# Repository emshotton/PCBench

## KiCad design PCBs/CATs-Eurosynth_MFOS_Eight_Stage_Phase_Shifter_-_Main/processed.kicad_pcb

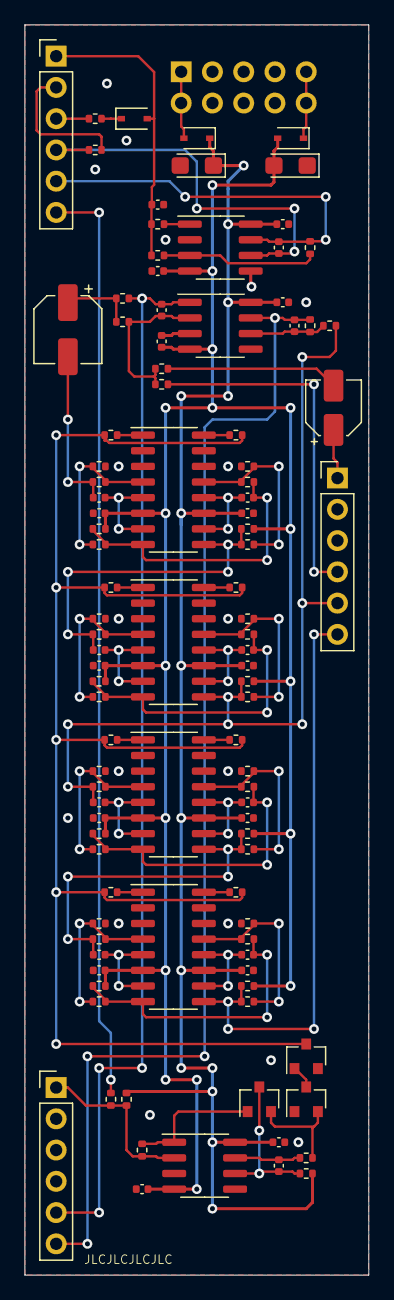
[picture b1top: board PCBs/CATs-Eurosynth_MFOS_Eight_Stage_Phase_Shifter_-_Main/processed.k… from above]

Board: 2 copper layers, 27.9 x 101.6 mm, 104 parts (1 on the bottom side), 62 nets.

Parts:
C1, C2, C3, C4, C5, C6, C8, C9, C10, C11, C12, C13, C14, C15: 100n; C_0402_1005Metric
C7, C16: 10µF/16V; CP_EIA-3216-18_Kemet-A
C17: 220n; C_0402_1005Metric
C18: 1µF/25V; CP_Elec_4x5.4
C19: 100p; C_0402_1005Metric
C20: 10µF/25V; CP_Elec_5x5.4
C21, C22, C23, C24, C25, C26, C27, C28: 4.7nF; C_0402_1005Metric
C29: 1µF/25V; C_0402_1005Metric
C30, C31: 22pF; C_0402_1005Metric
D1: 1N4148WS; D_SOD-323
D2, D3: 1N5817; D_SOD-323
J1: LFO; PinHeader_1x06_P2.54mm_Vertical
J2: CV_OUT; PinHeader_1x06_P2.54mm_Vertical
J3: In; PinHeader_1x06_P2.54mm_Vertical
J6: Power; Power_2x5_Vertical
Q1, Q3: MMBT3904; SOT-23
Q2: MMBT3906; SOT-23
R2, R5, R9, R14, R19, R33, R36, R39, R41, R55, R58, R60, R61: 10k; R_0402_1005Metric
R3: 43k; R_0402_1005Metric
R7: 270k; R_0402_1005Metric
R8, R31, R34, R37, R40, R51, R52, R53, R54: 1k; R_0402_1005Metric
R11: 430k; R_0402_1005Metric
R12, R17, R20: 100k; R_0402_1005Metric
R13: 1M; R_0402_1005Metric
R22: 2k; R_0402_1005Metric
R23, R25, R27, R29, R32, R35, R38, R42, R43, R45, R47, R49, R56, R57, R59, R62: 30k; R_0402_1005Metric
R24, R26, R28, R30, R44, R46, R48, R50, R64: 20k; R_0402_1005Metric
R65: 33k; R_0402_1005Metric
U1, U2, U3: TL072; SOIC-8_3.9x4.9mm_P1.27mm
U4, U5, U6, U7: LM13700; SOIC-16_3.9x9.9mm_P1.27mm

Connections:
+12V: C1.1, C2.1, C3.1, C4.1, C6.1, C7.1, C8.1, C12.1, D2.1, R11.2, R13.2, U1.8, U2.8, U3.8, U4.11, U5.11, U6.11, U7.11
+12V_In: D2.2, J6.+12V
-12V: C5.2, C9.2, C10.2, C11.2, C13.2, C14.2, C15.2, C16.2, D3.2, R33.1, R36.1, R39.1, R41.1, R55.1, R58.1, R60.1, R61.1, U1.4, U2.4, U3.4, U4.6, U5.6, U6.6, U7.6
-12V_In: D3.1, J6.-12V
CV: J2.1, R11.1, R12.1, R22.2, U3.2
Depth_CW: C17.1, J1.5, R20.1, U2.7
Depth_W: J1.6, R12.2
FB: J3.4, R9.2
GND: C1.2, C2.2, C3.2, C4.2, C5.1, C6.2, C7.2, C8.2, C9.1, C10.1, C11.1, C12.2, C13.1, C14.1, C15.1, C16.1, C29.2, J2.2, J2.3, J2.4, J3.2, J3.3, J6.GND, Q2.2, Q3.1, R31.1, R34.1, R37.1, R40.1, R51.1, R52.1, R53.1, R54.1, U1.3, U1.5, U2.2, U2.5, U3.3, U3.5, U4.3, U4.14, U5.3, U5.14, U6.3, U6.14, U7.3, U7.14
Iabc: Q2.3, R24.2, R26.2, R28.2, R30.2, R44.2, R46.2, R48.2, R50.2
In: C18.1, J3.1
Mode_In: J1.3, R8.1
Mode_Out: C17.2, J1.4, R17.1, U2.6
unnamed: C18.2, R5.2
unnamed: C19.1, R14.2, U3.7
unnamed: C19.2, Q1.3, R13.1, U3.6
unnamed: C20.1, R19.1, R65.2
unnamed: C21.1, U4.5, U4.7
unnamed: C22.1, U4.10, U4.12
unnamed: C22.2, R25.2, R32.1, R33.2, U4.8
unnamed: C23.1, U5.5, U5.7
unnamed: C23.2, R27.2, R35.1, R36.2, U4.9
unnamed: C24.1, U5.10, U5.12
unnamed: C24.2, R29.2, R38.1, R39.2, U5.8
unnamed: C25.1, U6.5, U6.7
unnamed: C26.1, U6.10, U6.12
unnamed: C26.2, R45.2, R55.2, R56.1, U6.8
unnamed: C27.1, U7.5, U7.7
unnamed: C27.2, R47.2, R57.1, R58.2, U6.9
unnamed: C28.1, U7.10, U7.12
unnamed: C28.2, R49.2, R59.1, R60.2, U7.8
unnamed: C30.2, R5.1, R9.1, R19.2, U1.2
unnamed: C31.2, R2.1, R3.2, U1.6
unnamed: D1.1, R8.2
unnamed: Q1.1, R22.1, U3.1
unnamed: Q1.2, Q3.2, R14.1
unnamed: Q2.1, Q3.3
unnamed: R7.2, R20.2, U2.3
unnamed: R23.1, R31.2, R32.2, U4.4
unnamed: R24.1, U4.1
unnamed: R25.1, R34.2, R35.2, U4.13
unnamed: R26.1, U4.16
unnamed: R27.1, R37.2, R38.2, U5.4
unnamed: R28.1, U5.1
unnamed: R29.1, R40.2, R42.2, U5.13
unnamed: R30.1, U5.16
unnamed: R43.1, R51.2, R56.2, U6.4
unnamed: R44.1, U6.1
unnamed: R45.1, R52.2, R57.2, U6.13
unnamed: R46.1, U6.16
unnamed: R47.1, R53.2, R59.2, U7.4
unnamed: R48.1, U7.1
unnamed: R49.1, R54.2, R62.2, U7.13
unnamed: R50.1, U7.16
unnamed: R64.2, U2.1
OUT4: C25.2, J3.5, R2.2, R41.2, R42.1, R43.2, U5.9
OUT8: J3.6, R61.2, R62.1, U7.9
Out1: C30.1, J2.5, R65.1, U1.1
Out2: C31.1, J2.6, R3.1, U1.7
PSS_In: C20.2, C21.2, R23.2
Rate_CW: C29.1, D1.2, J1.1, R7.1, R64.1
Rate_W: J1.2, R17.2

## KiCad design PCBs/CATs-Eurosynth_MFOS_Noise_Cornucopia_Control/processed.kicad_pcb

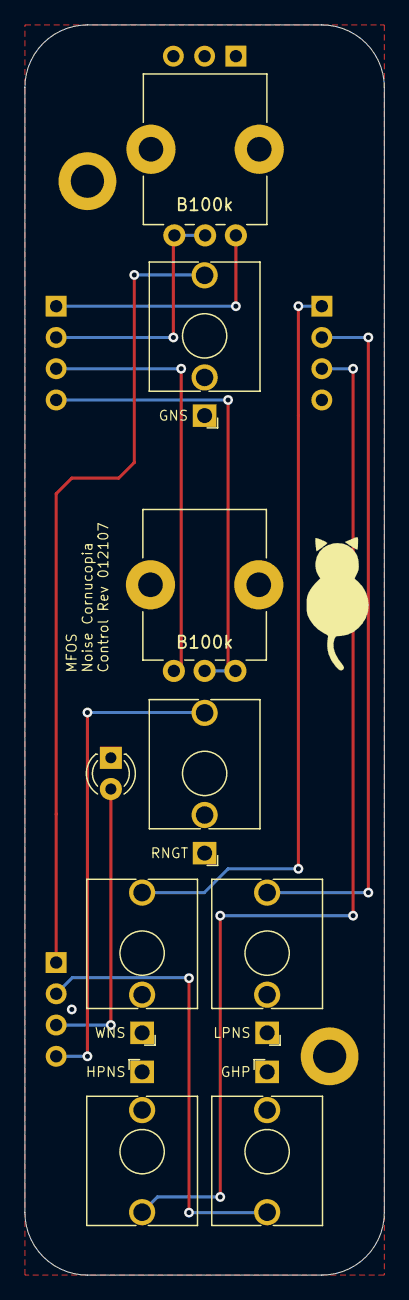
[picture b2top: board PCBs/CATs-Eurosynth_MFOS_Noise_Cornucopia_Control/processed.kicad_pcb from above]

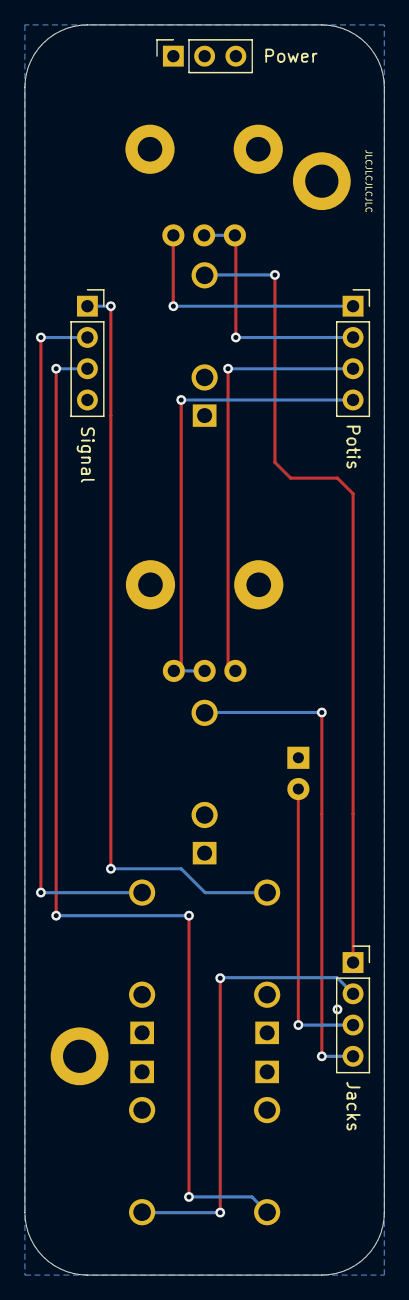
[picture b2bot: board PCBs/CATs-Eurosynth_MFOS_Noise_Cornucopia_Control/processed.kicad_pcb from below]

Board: 2 copper layers, 29.2 x 101.6 mm, 15 parts (4 on the bottom side), 12 nets.

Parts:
D1: LED; LED_D3.0mm
H1, H2: MountingHole_Pad; MountingHole_2.7mm_M2.5_DIN965_Pad
J1: WNS; Jack_3.5mm_QingPu_WQP-PJ398SM_Vertical_CircularHoles
J2: Power; PinSocket_1x03_P2.54mm_Vertical
J3: Signal; PinSocket_1x04_P2.54mm_Vertical
J4: LPNS; Jack_3.5mm_QingPu_WQP-PJ398SM_Vertical_CircularHoles
J5: HPNS; Jack_3.5mm_QingPu_WQP-PJ398SM_Vertical_CircularHoles
J6: Potis; PinSocket_1x04_P2.54mm_Vertical
J7: Jacks; PinSocket_1x04_P2.54mm_Vertical
J8: GNS; Jack_3.5mm_QingPu_WQP-PJ398SM_Vertical_CircularHoles
J9: GHP; Jack_3.5mm_QingPu_WQP-PJ398SM_Vertical_CircularHoles
J10: RNGT; Jack_3.5mm_QingPu_WQP-PJ398SM_Vertical_CircularHoles
R18, R28: B100k; Potentiometer_Alps_RK09K_Single_Vertical

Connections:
GHP: J7.2, J9.T
GND: D1.1, H1.1, H2.1, J1.S, J2.2, J4.S, J5.S, J8.S, J9.S, J10.S
GNS: J7.1, J8.T
GRNS1: J6.1, R18.1
GRNS2: J6.2, R18.2, R18.3
GTF1: J6.3, R28.3
GTF2: J6.4, R28.1, R28.2
HPNS: J3.3, J5.T
LEDA: D1.2, J7.3
LPNS: J3.2, J4.T
RNGT: J7.4, J10.T
WNS: J1.T, J3.1

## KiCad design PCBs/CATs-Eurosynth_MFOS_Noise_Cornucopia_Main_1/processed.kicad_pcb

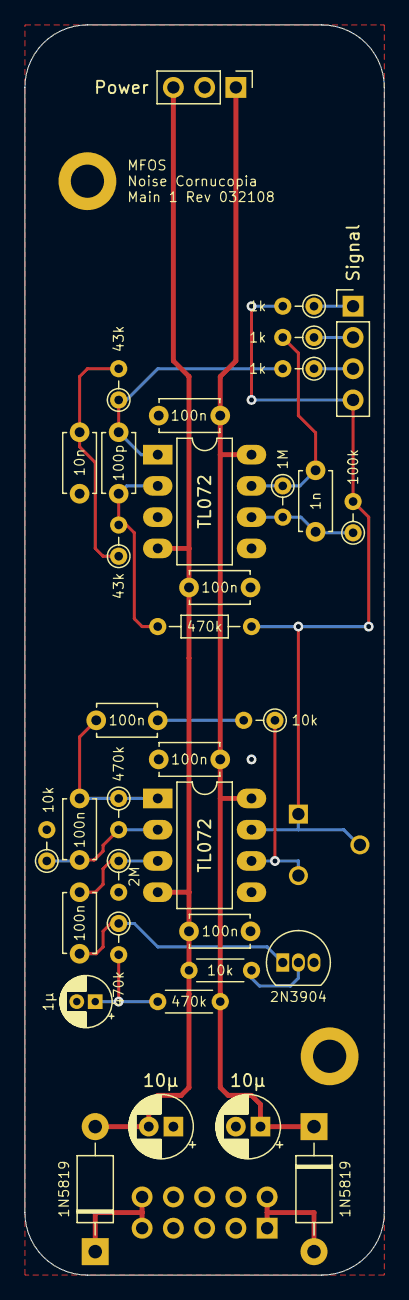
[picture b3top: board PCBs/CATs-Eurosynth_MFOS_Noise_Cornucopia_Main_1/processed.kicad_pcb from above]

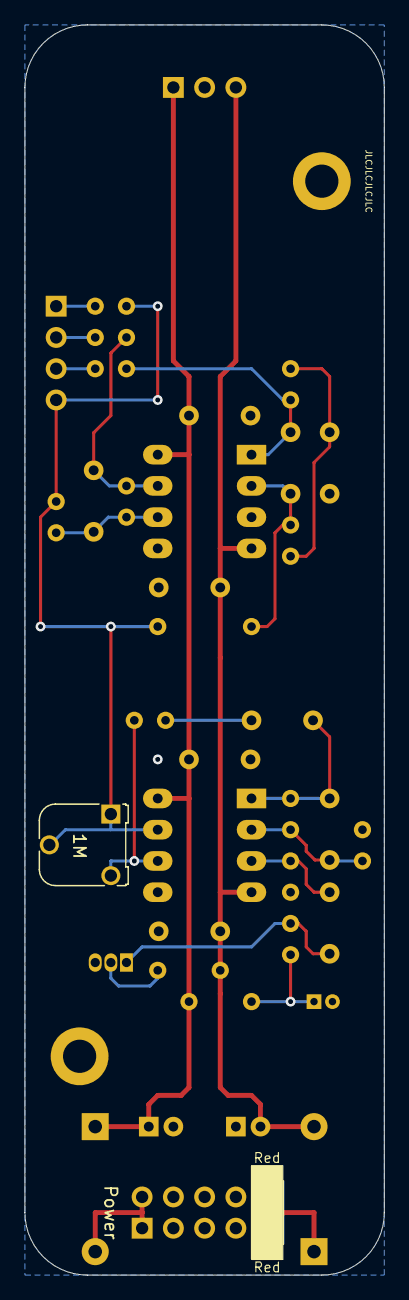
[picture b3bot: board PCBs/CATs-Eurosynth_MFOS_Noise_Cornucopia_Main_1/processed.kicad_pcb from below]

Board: 2 copper layers, 29.2 x 101.6 mm, 39 parts (2 on the bottom side), 22 nets.

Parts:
C1, C2, C4, C5, C7, C10, C12: 100n; C_Disc_D4.7mm_W2.5mm_P5.00mm
C3: 1n; C_Disc_D4.7mm_W2.5mm_P5.00mm
C6, C11: 10µ; CP_Radial_D5.0mm_P2.00mm
C9: 100p; C_Disc_D4.7mm_W2.5mm_P5.00mm
C14: 10n; C_Disc_D4.7mm_W2.5mm_P5.00mm
C18: 1µ; CP_Radial_D4.0mm_P1.50mm
D4, D5: 1N5819; D_DO-41_SOD81_P10.16mm_Horizontal
H1, H2: MountingHole_Pad; MountingHole_2.7mm_M2.5_DIN965_Pad
J1: Signal; PinHeader_1x04_P2.54mm_Vertical
J2: Power; PinHeader_1x03_P2.54mm_Vertical
J4: Power; Power_2x5_Vertical
Q1: 2N3904; TO-92_Inline
R1, R3, R11: 1k; R_Axial_DIN0204_L3.6mm_D1.6mm_P2.54mm_Vertical
R2, R10: 470k; R_Axial_DIN0204_L3.6mm_D1.6mm_P2.54mm_Vertical
R4: 2M; R_Axial_DIN0204_L3.6mm_D1.6mm_P2.54mm_Vertical
R5, R9: 10k; R_Axial_DIN0204_L3.6mm_D1.6mm_P2.54mm_Vertical
R6: 100k; R_Axial_DIN0204_L3.6mm_D1.6mm_P2.54mm_Vertical
R7: 1M; R_Axial_DIN0204_L3.6mm_D1.6mm_P2.54mm_Vertical
R8: 1M; Potentiometer_Runtron_RM-065_Vertical
R12: 470k; R_Axial_DIN0204_L3.6mm_D1.6mm_P7.62mm_Horizontal
R16, R17: 43k; R_Axial_DIN0204_L3.6mm_D1.6mm_P2.54mm_Vertical
R33: 470k; R_Axial_DIN0204_L3.6mm_D1.6mm_P5.08mm_Horizontal
R34: 10k; R_Axial_DIN0204_L3.6mm_D1.6mm_P5.08mm_Horizontal
U1, U2: TL072; DIP-8_W7.62mm_LongPads

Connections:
+12V: C5.2, C6.1, C7.2, D4.1, J2.1, R33.1, U1.8, U2.8
+12VA: D4.2, J4.+12V
-12V: C10.1, C11.2, C12.1, D5.2, J2.3, R34.2, U1.4, U2.4
-12VA: D5.1, J4.-12V
GND: C5.1, C6.2, C7.1, C10.2, C11.1, C12.2, C14.1, C18.2, H1.1, H2.1, J2.2, J4.GND, R4.2, R9.2, U1.5, U2.3, U2.5
HPNS: J1.3, R11.1
LPNS: J1.2, R3.1
NOISE_INT: J1.4, R1.2, R6.2, R8.1, R8.2, R12.2, U1.7
unnamed: C1.1, R4.1, U1.3
unnamed: C1.2, Q1.1, R2.1
unnamed: C2.1, R5.2
unnamed: C2.2, C4.1, R10.1, U1.1
unnamed: C3.1, R3.2, R7.1, U2.7
unnamed: C3.2, R6.1, R7.2, U2.6
unnamed: C4.2, R9.1, R10.2, U1.2
unnamed: C9.1, R12.1, R16.2, U2.2
unnamed: C9.2, R11.2, R17.1, U2.1
unnamed: C14.2, R16.1, R17.2
unnamed: C18.1, R2.2, R33.2
unnamed: Q1.2, R34.1
unnamed: R5.1, R8.3, U1.6
WNS: J1.1, R1.1

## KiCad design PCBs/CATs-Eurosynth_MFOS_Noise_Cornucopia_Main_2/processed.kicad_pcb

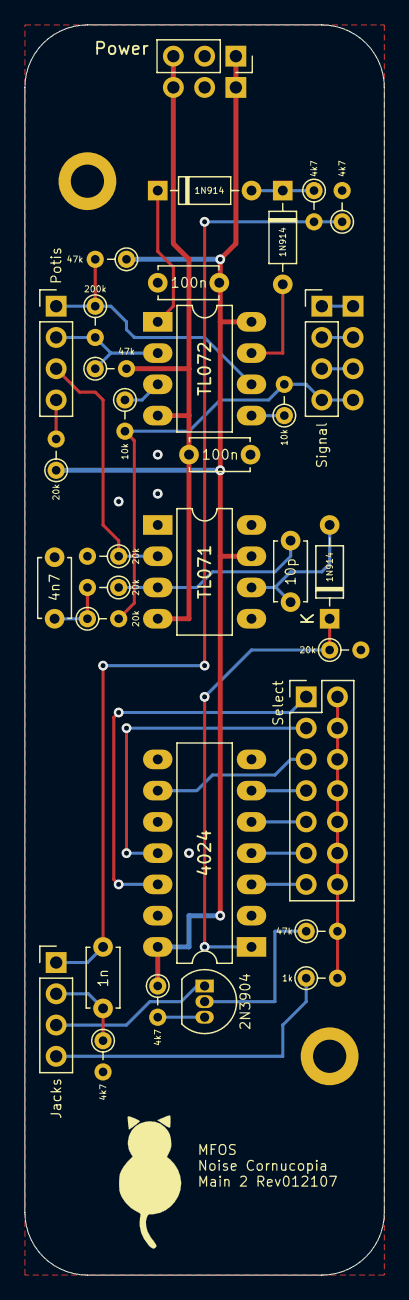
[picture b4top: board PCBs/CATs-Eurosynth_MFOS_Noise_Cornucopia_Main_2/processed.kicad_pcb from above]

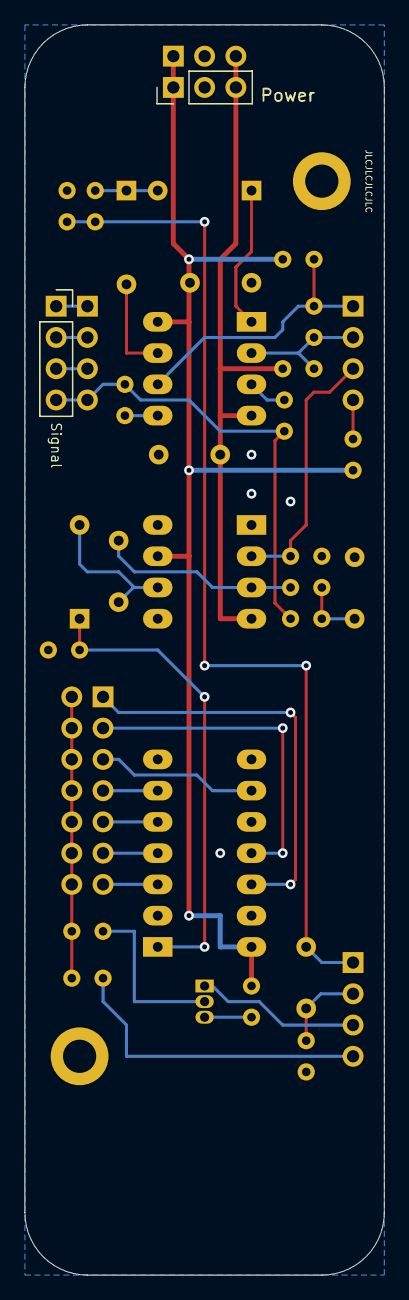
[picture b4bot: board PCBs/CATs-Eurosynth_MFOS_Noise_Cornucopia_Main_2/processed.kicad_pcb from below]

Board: 2 copper layers, 29.2 x 101.6 mm, 37 parts (2 on the bottom side), 34 nets.

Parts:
C8, C13: 100n; C_Disc_D4.7mm_W2.5mm_P5.00mm
C15: 1n; C_Disc_D4.7mm_W2.5mm_P5.00mm
C16: 10p; C_Disc_D4.7mm_W2.5mm_P5.00mm
C17: 4n7; C_Disc_D4.7mm_W2.5mm_P5.00mm
D1, D2, D3: 1N914; D_DO-35_SOD27_P7.62mm_Horizontal
H1, H2: MountingHole_Pad; MountingHole_2.7mm_M2.5_DIN965_Pad
J1: Select; PinHeader_2x07_P2.54mm_Vertical
J2: Power; PinSocket_1x03_P2.54mm_Vertical
J3: Signal; PinSocket_1x04_P2.54mm_Vertical
J4: Signal; PinHeader_1x04_P2.54mm_Vertical
J5: Power; PinHeader_1x03_P2.54mm_Vertical
J6: Potis; PinHeader_1x04_P2.54mm_Vertical
J7: Jacks; PinHeader_1x04_P2.54mm_Vertical
Q2: 2N3904; TO-92_Inline
R13, R22, R30: 47k; R_Axial_DIN0204_L3.6mm_D1.6mm_P2.54mm_Vertical
R14, R20: 10k; R_Axial_DIN0204_L3.6mm_D1.6mm_P2.54mm_Vertical
R15, R21, R23, R24: 4k7; R_Axial_DIN0204_L3.6mm_D1.6mm_P2.54mm_Vertical
R19: 200k; R_Axial_DIN0204_L3.6mm_D1.6mm_P2.54mm_Vertical
R25, R26, R27, R29, R31: 20k; R_Axial_DIN0204_L3.6mm_D1.6mm_P2.54mm_Vertical
R32: 1k; R_Axial_DIN0204_L3.6mm_D1.6mm_P2.54mm_Vertical
U3: TL072; DIP-8_W7.62mm_LongPads
U4: TL071; DIP-8_W7.62mm_LongPads
U5: 4024; DIP-14_W7.62mm_LongPads

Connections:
+12V: C8.2, J2.1, J5.1, R13.1, R24.1, R25.1, U3.8, U4.7, U5.14
-12V: C13.1, J2.3, J5.3, R22.2, U3.4, U4.4
GHP: C15.2, J7.2, R23.1
GND: C8.1, C13.2, C17.2, H1.1, H2.1, J2.2, J5.2, R21.2, R23.2, R29.2, R31.2, U5.2, U5.7
GNS: C15.1, J7.1, R15.2, R21.1
GRNS1: J6.1, R13.2, R19.1, U3.6
GRNS2: J6.2, R19.2, R22.1, U3.2
GTF1: J6.3, R31.1, U4.2
GTF2: J6.4, R25.2
LEDA: J7.3, Q2.1
NOISE_INT: J3.4, J4.4, R14.2, R20.2, R26.2
unnamed: C16.1, R27.1, U4.3
unnamed: C16.2, D3.2, U4.6
unnamed: C17.1, R26.1, R27.2
unnamed: D1.1, D2.2, R15.1
unnamed: D1.2, U3.7
unnamed: D2.1, U3.1
unnamed: D3.1, R29.1, U5.1
unnamed: J1.1, U5.12
unnamed: J1.3, U5.11
unnamed: J1.5, U5.9
unnamed: J1.7, U5.6
unnamed: J1.9, U5.5
unnamed: J1.2, J1.4, J1.6, J1.8, J1.10, J1.12, J1.14, R30.2, R32.2
unnamed: J1.11, U5.4
unnamed: J1.13, U5.3
unnamed: J3.1, J4.1
unnamed: J3.2, J4.2
unnamed: J3.3, J4.3
unnamed: Q2.2, R30.1
unnamed: Q2.3, R24.2
unnamed: R14.1, U3.5
unnamed: R20.1, U3.3
RNGT: J7.4, R32.1

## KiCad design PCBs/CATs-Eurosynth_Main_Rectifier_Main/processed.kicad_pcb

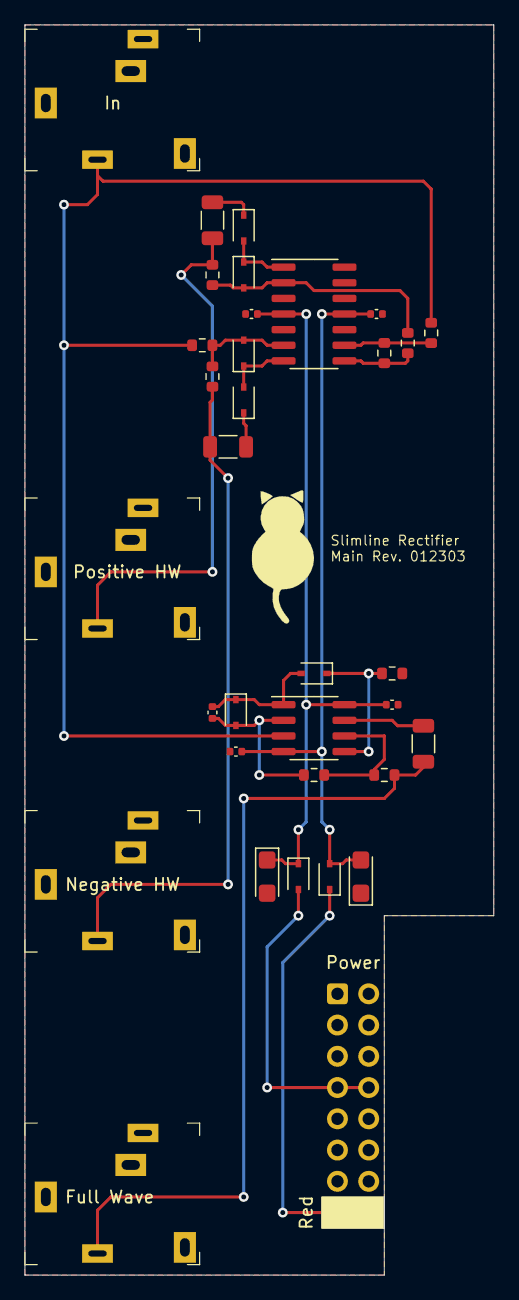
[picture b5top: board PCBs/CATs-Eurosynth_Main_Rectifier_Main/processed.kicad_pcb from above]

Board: 2 copper layers, 38.1 x 101.6 mm, 34 parts (0 on the bottom side), 22 nets.

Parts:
C1: 22p; C_0402_1005Metric
C2, C5: 10uF/16V; CP_EIA-3216-18_Kemet-A
C3, C4, C6, C7: 100n; C_0402_1005Metric
D1, D2, D3, D4, D5, D6: 1N4148WS; D_SOD-323
D7, D8: 1N5819WS; D_SOD-323
J1: Full Wave; Jack_3.5mm_QingPu_WQP-PJ324M
J2: Negative HW; Jack_3.5mm_QingPu_WQP-PJ324M
J3: In; Jack_3.5mm_QingPu_WQP-PJ324M
J4: Positive HW; Jack_3.5mm_QingPu_WQP-PJ324M
J5: Power; Power_2x8_Horizontal
R1, R2, R4, R5, R6, R8, R9, R10, R11: 100k; R_0603_1608Metric
R3, R7, R12: 1k; R_1206_3216Metric
U1: TL082CDT; SOIC-8_3.9x4.9mm_P1.27mm
U2: TL084CDT; SOIC-14_3.9x8.7mm_P1.27mm

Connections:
+12V: C2.1, C3.1, C4.2, D7.1 (K), U1.8 (V+), U2.4 (V+)
-12V: C5.2, C6.2, C7.1, D8.2 (A), U1.4 (V-), U2.11 (V-)
GND: C2.2, C3.2, C4.1, C5.1, C6.1, C7.2, J1.S, J2.S, J3.S, J3.TN, J4.S, J5.GND, R4.1, U2.3 (+), U2.5 (+), U2.10 (+)
unnamed: C1.1, D1.2 (A), R1.1, U1.2 (-)
unnamed: C1.2, D1.1 (K), D2.2 (A), U1.1
unnamed: D2.1 (K), R4.2, U1.5 (+)
unnamed: D3.1 (K), D4.2 (A), U2.7
unnamed: D3.2 (A), R5.1, R6.2, U2.6 (-)
unnamed: D4.1 (K), R7.1
unnamed: D5.1 (K), D6.2 (A), U2.1
unnamed: D5.2 (A), R8.1, R11.2, U2.2 (-)
unnamed: D6.1 (K), R12.1
unnamed: D7.2 (A), J5.+12V
unnamed: D8.1 (K), J5.-12V
unnamed: J1.T, R2.2, R3.2
unnamed: J2.T, R5.2, R7.2
unnamed: J3.T, R6.1, R10.1, U1.3 (+)
unnamed: J4.T, R8.2, R12.2
unnamed: R1.2, R2.1, U1.6 (-)
unnamed: R3.1, U1.7
unnamed: R9.2, R11.1, U2.8
unnamed: R9.1, R10.2, U2.9 (-)

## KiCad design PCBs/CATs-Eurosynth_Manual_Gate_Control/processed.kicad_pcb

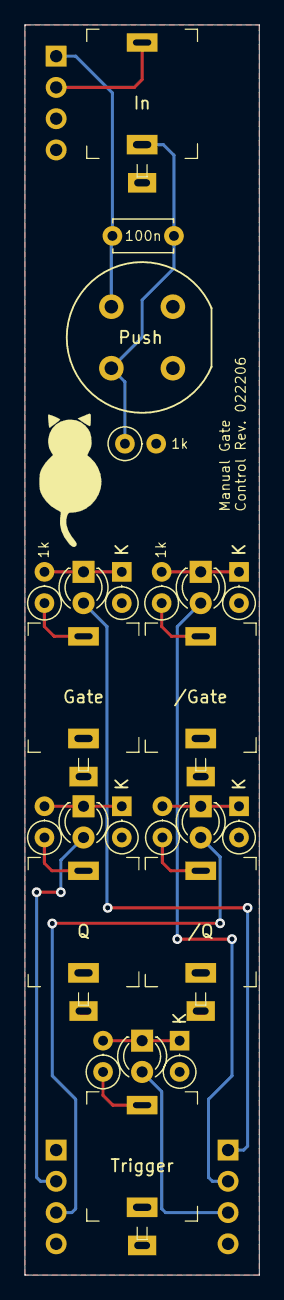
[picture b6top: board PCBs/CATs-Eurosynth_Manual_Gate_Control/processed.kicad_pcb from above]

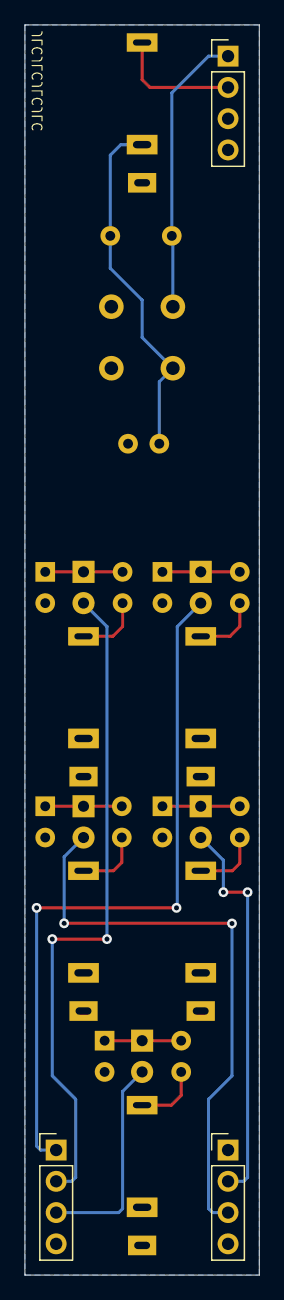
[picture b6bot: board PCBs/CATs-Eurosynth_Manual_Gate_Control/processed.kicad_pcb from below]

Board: 2 copper layers, 19.1 x 101.6 mm, 27 parts (3 on the bottom side), 19 nets.

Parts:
C1: 100n; C_Disc_D4.7mm_W2.5mm_P5.00mm
D1, D2, D5, D7, D8: 1N4733A; D_DO-35_SOD27_P2.54mm_Vertical_KathodeUp
D3, D4, D6, D10, D11: LED; LED_D3.0mm
J1: Q; Jack_3.5mm_QingPu_WQP-PJ301M-12
J2: Trigger; Jack_3.5mm_QingPu_WQP-PJ301M-12
J4: /Q; Jack_3.5mm_QingPu_WQP-PJ301M-12
J5: Gate; Jack_3.5mm_QingPu_WQP-PJ301M-12
J6: /Gate; Jack_3.5mm_QingPu_WQP-PJ301M-12
J7: In; Jack_3.5mm_QingPu_WQP-PJ301M-12
J8: In; PinHeader_1x04_P2.54mm_Vertical
J9: Q_Qq; PinHeader_1x04_P2.54mm_Vertical
J10: Gate; PinHeader_1x04_P2.54mm_Vertical
R1, R13, R15, R26, R34, R38: 1k; R_Axial_DIN0207_L6.3mm_D2.5mm_P2.54mm_Vertical
SW1: Push; Push_E-Switch_KS01Q01

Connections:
+12V: C1.1, J8.1, SW1.2
GND: D1.2, D2.2, D5.2, D7.2, D8.2, J1.S, J2.S, J4.S, J5.S, J6.S, J7.S, J8.3, J8.4, J9.1, J9.4, J10.4, R1.2
Gate_Pin: D10.2, J10.1
Gateq_Pin: D11.2, J10.2
In_Pin: J7.T, J8.2
unnamed: C1.2, J7.TN, R1.1, SW1.1
unnamed: D1.1, D11.1, R38.2
unnamed: D2.1, D3.1, R13.2
unnamed: D4.1, D8.1, R15.2
unnamed: D5.1, D6.1, R26.2
unnamed: D7.1, D10.1, R34.2
unnamed: J1.T, R13.1
unnamed: J2.T, R15.1
unnamed: J4.T, R26.1
unnamed: J5.T, R34.1
unnamed: J6.T, R38.1
Q_Pin: D3.2, J9.2
Qq_Pin: D6.2, J9.3
Trigger_Pin: D4.2, J10.3

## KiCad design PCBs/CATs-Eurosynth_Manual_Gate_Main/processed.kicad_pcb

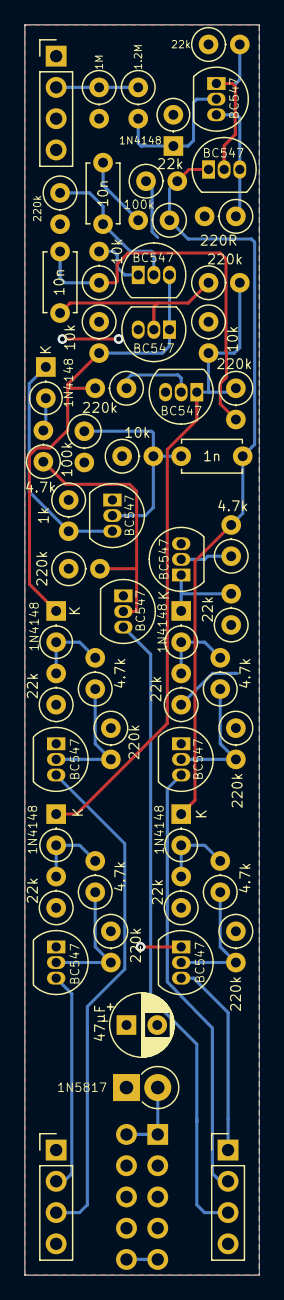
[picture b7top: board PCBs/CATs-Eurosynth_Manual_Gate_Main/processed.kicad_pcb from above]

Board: 2 copper layers, 19.1 x 101.6 mm, 59 parts (1 on the bottom side), 35 nets.

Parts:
C2: 1n; C_Disc_D4.7mm_W2.5mm_P5.00mm
C3, C4: 10n; C_Disc_D4.7mm_W2.5mm_P5.00mm
C5: 47µF; CP_Radial_D5.0mm_P2.50mm
D1, D2, D5, D8, D9, D12: 1N4148; D_DO-35_SOD27_P2.54mm_Vertical_KathodeUp
D7: 1N5817; D_DO-41_SOD81_P2.54mm_Vertical_KathodeUp
J3: Power; Power_2x5_Vertical
J8: In; PinHeader_1x04_P2.54mm_Vertical
J9: Q_Qq; PinHeader_1x04_P2.54mm_Vertical
J10: Gate; PinHeader_1x04_P2.54mm_Vertical
Q1, Q2, Q3, Q4, Q5, Q6, Q7, Q8, Q9, Q10, Q11, Q12: BC547; TO-92_Inline
R1, R3: 100k; R_Axial_DIN0207_L6.3mm_D2.5mm_P2.54mm_Vertical
R2, R16, R18, R23: 10k; R_Axial_DIN0207_L6.3mm_D2.5mm_P2.54mm_Vertical
R4: 1k; R_Axial_DIN0207_L6.3mm_D2.5mm_P2.54mm_Vertical
R5, R19, R27, R31, R33, R41, R43: 22k; R_Axial_DIN0207_L6.3mm_D2.5mm_P2.54mm_Vertical
R6, R10, R21, R28, R29, R35: 4.7k; R_Axial_DIN0207_L6.3mm_D2.5mm_P2.54mm_Vertical
R8, R9, R11, R17, R20, R22, R25, R30, R36: 220k; R_Axial_DIN0207_L6.3mm_D2.5mm_P2.54mm_Vertical
R39: 1M; R_Axial_DIN0207_L6.3mm_D2.5mm_P2.54mm_Vertical
R40: 1.2M; R_Axial_DIN0207_L6.3mm_D2.5mm_P2.54mm_Vertical
R42: 220R; R_Axial_DIN0207_L6.3mm_D2.5mm_P2.54mm_Vertical

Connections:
+12V: C5.1, D7.1, J8.1, Q1.1, Q3.1, Q4.1, Q7.1, Q9.1, Q10.1, R1.2, R5.1, R16.1, R19.1, R23.1, R27.1, R31.1, R33.1, R41.1, R43.1
+12VA: D7.2, J3.+12V
GND: C5.2, D12.2, J3.GND, J8.3, J8.4, J9.1, J9.4, J10.4, Q5.3, Q6.3, Q8.3, R2.1, R4.1, R8.2, R9.1, R11.1, R22.1, R30.1, R36.1, R39.2, R42.2
Gate_Pin: J10.1, Q9.3
Gateq_Pin: J10.2, Q10.3
In_Pin: J8.2, R39.1, R40.1
unnamed: C2.1, Q1.2, R1.1, R2.2
unnamed: C3.1, Q2.2, R8.1
unnamed: C3.2, R3.2
unnamed: C4.1, R18.1, R25.2
unnamed: C4.2, Q5.2, R20.1
unnamed: D1.2, R5.2, R6.2
unnamed: D2.1, Q1.3, R4.2
unnamed: D2.2, R10.2
unnamed: D5.2, R19.2, R21.2
unnamed: D8.2, R27.2, R29.2
unnamed: D9.1, Q8.1, R31.2
unnamed: D9.2, R33.2, R35.2
unnamed: D12.1, Q11.2, R40.2
unnamed: Q2.1, R18.2
unnamed: Q3.2, R6.1, R9.2
unnamed: Q4.2, R10.1, R11.2
unnamed: Q6.2, R17.1
unnamed: Q7.2, R21.1, R22.2
unnamed: Q8.2, R28.1
unnamed: Q9.2, R29.1, R30.2
unnamed: Q10.2, R35.1, R36.2
unnamed: Q11.1, Q12.2, R41.2
unnamed: Q11.3, Q12.3, R42.1
Ping: C2.2, D8.1, Q12.1, R3.1, R28.2, R43.2
Q: D1.1, Q6.1, R20.2, R23.2, R25.1
Q_Pin: J9.2, Q3.3
Qq_Pin: J9.3, Q7.3
Qquer: D5.1, Q2.3, Q5.1, R16.2, R17.2
Trigger_Pin: J10.3, Q4.3

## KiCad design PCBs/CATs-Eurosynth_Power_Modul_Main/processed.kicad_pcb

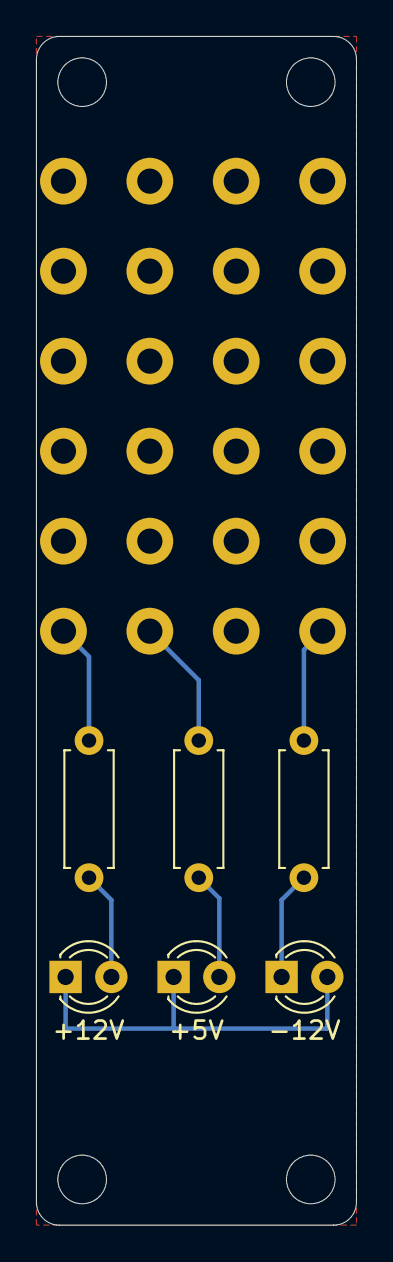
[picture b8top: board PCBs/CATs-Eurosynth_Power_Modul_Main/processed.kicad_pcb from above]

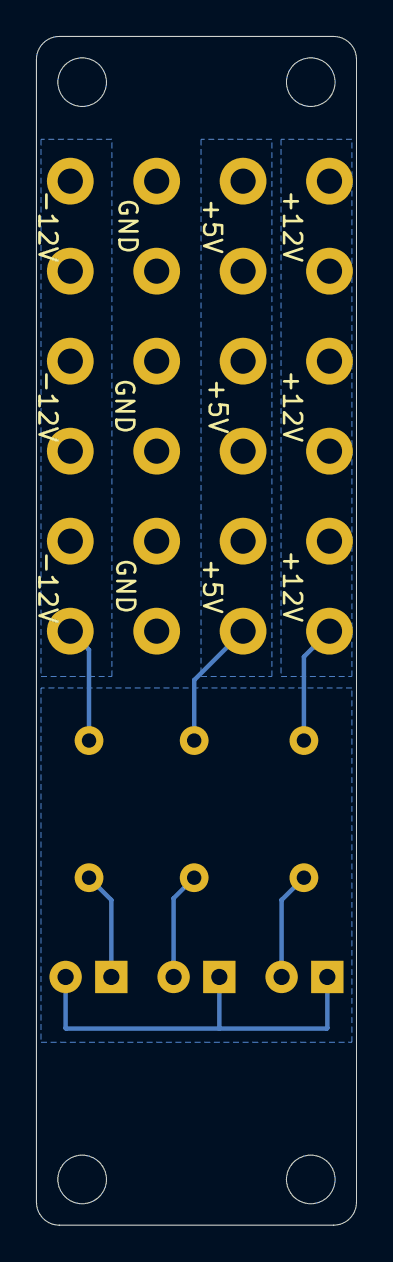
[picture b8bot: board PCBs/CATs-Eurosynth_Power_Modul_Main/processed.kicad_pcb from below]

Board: 2 copper layers, 17.8 x 66.0 mm, 22 parts (4 on the bottom side), 7 nets.

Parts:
D1: +12V; LED_D3.0mm
D2: +5V; LED_D3.0mm
D3: -12V; LED_D3.0mm
H1, H2, H3, H4: MountingHole_Pad; MountingHole_2.7mm
J1, J5, J9: +12V; 03866b.68_6.3mm_FASTON
J2, J6, J10: +5V; 03866b.68_6.3mm_FASTON
J3, J7, J11: GND; 03866b.68_6.3mm_FASTON
J4, J8, J12: -12V; 03866b.68_6.3mm_FASTON
R1, R3: 1k; R_Axial_DIN0207_L6.3mm_D2.5mm_P7.62mm_Horizontal
R2: 200R; R_Axial_DIN0207_L6.3mm_D2.5mm_P7.62mm_Horizontal

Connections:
+5V: J2.1, J6.1, J10.1, R2.1
+12V: J1.1, J5.1, J9.1, R1.1
-12V: J4.1, J8.1, J12.1, R3.2
GND: D1.1, D2.1, D3.2, H1.1, H2.1, H3.1, H4.1, J3.1, J7.1, J11.1
unnamed: D1.2, R1.2
unnamed: D2.2, R2.2
unnamed: D3.1, R3.1
